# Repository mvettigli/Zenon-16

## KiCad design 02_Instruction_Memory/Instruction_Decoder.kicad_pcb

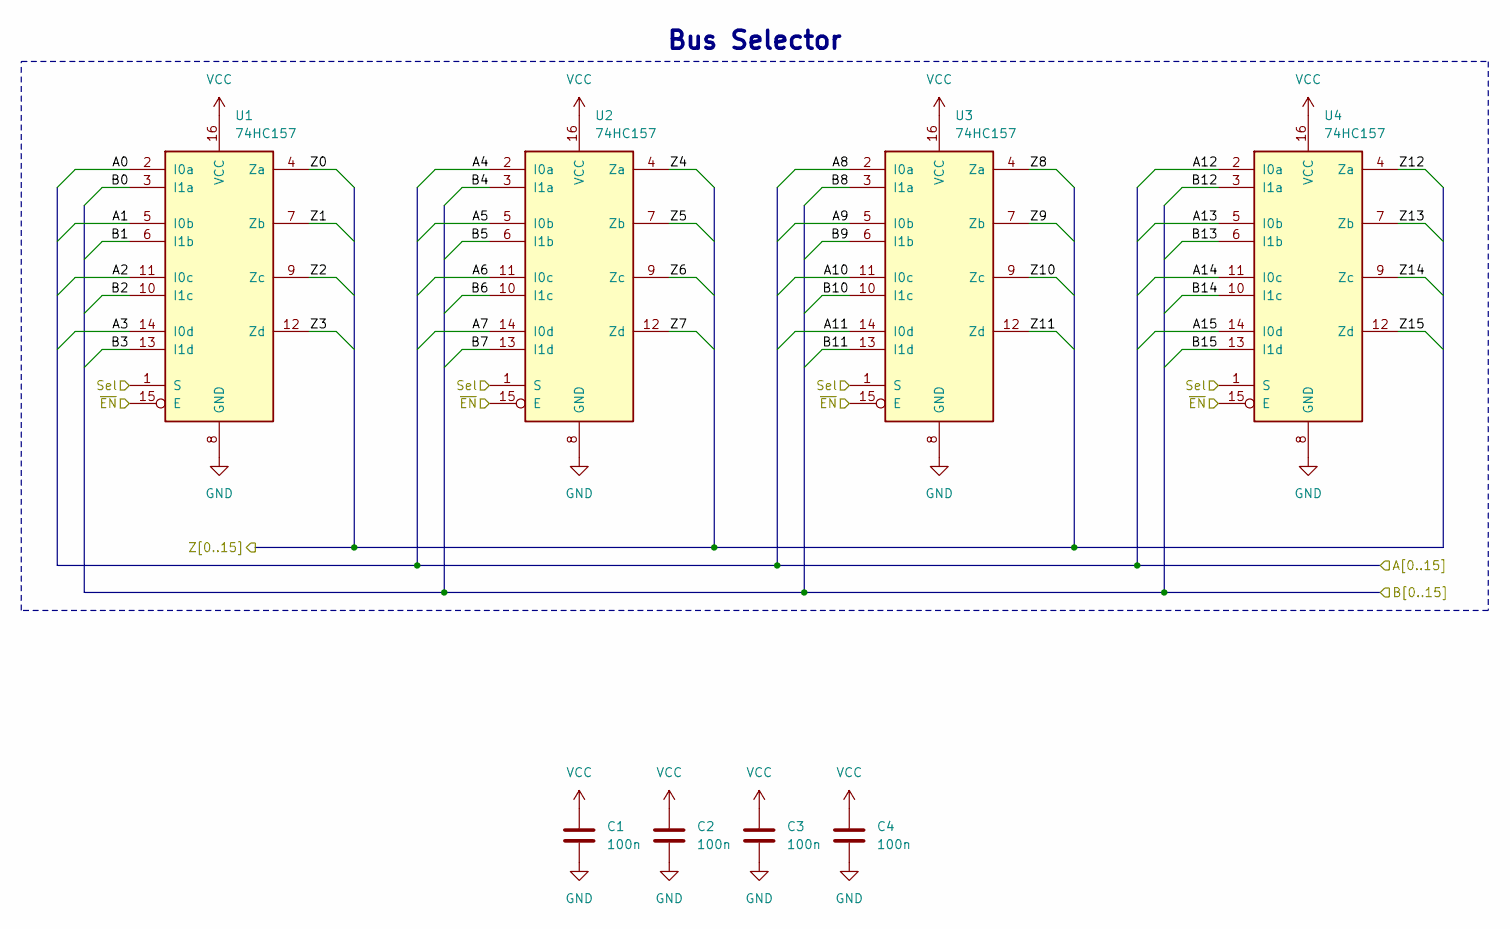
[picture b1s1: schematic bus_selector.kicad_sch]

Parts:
C1, C2, C3, C4: 100n; C_0603_1608Metric
U1, U2, U3, U4: 74HC157; TSSOP-16_4.4x5mm_P0.65mm

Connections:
/A0: U1.4 (Za); also elsewhere on the board
/A1: U1.7 (Zb); also elsewhere on the board
/A2: U1.9 (Zc); also elsewhere on the board
/A3: U1.12 (Zd); also elsewhere on the board
/A4: U2.4 (Za); also elsewhere on the board
/A5: U2.7 (Zb); also elsewhere on the board
/A6: U2.9 (Zc); also elsewhere on the board
/A7: U2.12 (Zd); also elsewhere on the board
/A8: U3.4 (Za); also elsewhere on the board
/A9: U3.7 (Zb); also elsewhere on the board
/A10: U3.9 (Zc); also elsewhere on the board
/A11: U3.12 (Zd); also elsewhere on the board
/A12: U4.4 (Za); also elsewhere on the board
/A13: U4.7 (Zb); also elsewhere on the board
/A14: U4.9 (Zc); also elsewhere on the board
/A15: U4.12 (Zd); also elsewhere on the board
/Address selector/A0: U1.2 (I0a); also elsewhere on the board
/Address selector/A1: U1.5 (I0b); also elsewhere on the board
/Address selector/A2: U1.11 (I0c); also elsewhere on the board
/Address selector/A3: U1.14 (I0d); also elsewhere on the board
/Address selector/A4: U2.2 (I0a); also elsewhere on the board
/Address selector/A5: U2.5 (I0b); also elsewhere on the board
/Address selector/A6: U2.11 (I0c); also elsewhere on the board
/Address selector/A7: U2.14 (I0d); also elsewhere on the board
/Address selector/A8: U3.2 (I0a); also elsewhere on the board
/Address selector/A9: U3.5 (I0b); also elsewhere on the board
/Address selector/A10: U3.11 (I0c); also elsewhere on the board
/Address selector/A11: U3.14 (I0d); also elsewhere on the board
/Address selector/A12: U4.2 (I0a); also elsewhere on the board
/Address selector/A13: U4.5 (I0b); also elsewhere on the board
/Address selector/A14: U4.11 (I0c); also elsewhere on the board
/Address selector/A15: U4.14 (I0d); also elsewhere on the board
/MR0: U1.3 (I1a)
/MR1: U1.6 (I1b)
/MR2: U1.10 (I1c)
/MR3: U1.13 (I1d)
/MR4: U2.3 (I1a)
/MR5: U2.6 (I1b)
/MR6: U2.10 (I1c)
/MR7: U2.13 (I1d)
/MR8: U3.3 (I1a)
/MR9: U3.6 (I1b)
/MR10: U3.10 (I1c)
/MR11: U3.13 (I1d)
/MR12: U4.3 (I1a)
/MR13: U4.6 (I1b)
/MR14: U4.10 (I1c)
/MR15: U4.13 (I1d)
~PC/MR: U1.1 (S), U2.1 (S), U3.1 (S), U4.1 (S)

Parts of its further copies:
C16, C17, C18, C19, C26, C27, C28, C29: 100n; C_0603_1608Metric
U15, U16, U17, U18, U25, U26, U27, U28: 74HC157; TSSOP-16_4.4x5mm_P0.65mm

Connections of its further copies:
/ImR0: U25.2 (I0a); also elsewhere on the board
/ImR1: U25.5 (I0b); also elsewhere on the board
/ImR2: U25.11 (I0c); also elsewhere on the board
/ImR3: U25.14 (I0d); also elsewhere on the board
/ImR4: U26.2 (I0a); also elsewhere on the board
/ImR5: U26.5 (I0b); also elsewhere on the board
/ImR6: U26.11 (I0c); also elsewhere on the board
/ImR7: U26.14 (I0d); also elsewhere on the board
/ImR8: U27.2 (I0a); also elsewhere on the board
/ImR9: U27.5 (I0b); also elsewhere on the board
/ImR10: U27.11 (I0c); also elsewhere on the board
/ImR11: U27.14 (I0d); also elsewhere on the board
/ImR12: U28.2 (I0a); also elsewhere on the board
/ImR13: U28.5 (I0b); also elsewhere on the board
/ImR14: U28.11 (I0c); also elsewhere on the board
/ImR15: U28.14 (I0d); also elsewhere on the board
/InR0: U15.3 (I1a); also elsewhere on the board
/InR1: U15.6 (I1b); also elsewhere on the board
/InR2: U15.10 (I1c); also elsewhere on the board
/InR3: U15.13 (I1d); also elsewhere on the board
/InR4: U16.3 (I1a); also elsewhere on the board
/InR5: U16.6 (I1b); also elsewhere on the board
/InR6: U16.10 (I1c); also elsewhere on the board
/InR7: U16.13 (I1d); also elsewhere on the board
/InR8: U17.3 (I1a); also elsewhere on the board
/InR9: U17.6 (I1b); also elsewhere on the board
/InR10: U17.10 (I1c); also elsewhere on the board
/InR11: U17.13 (I1d); also elsewhere on the board
/InR12: U18.3 (I1a); also elsewhere on the board
/InR13: U18.6 (I1b); also elsewhere on the board
/InR14: U18.10 (I1c); also elsewhere on the board
/InR15: U18.13 (I1d); also elsewhere on the board
/Program counter/1R0: U15.2 (I0a)
/Program counter/1R1: U15.5 (I0b)
/Program counter/1R2: U15.11 (I0c)
/Program counter/1R3: U15.14 (I0d)
/Program counter/1R4: U16.2 (I0a)
/Program counter/1R5: U16.5 (I0b)
/Program counter/1R6: U16.11 (I0c)
/Program counter/1R7: U16.14 (I0d)
/Program counter/1R8: U17.2 (I0a)
/Program counter/1R9: U17.5 (I0b)
/Program counter/1R10: U17.11 (I0c)
/Program counter/1R11: U17.14 (I0d)
/Program counter/1R12: U18.2 (I0a)
/Program counter/1R13: U18.5 (I0b)
/Program counter/1R14: U18.11 (I0c)
/Program counter/1R15: U18.14 (I0d)
/Program counter/B0: U15.4 (Za); also elsewhere on the board
/Program counter/B1: U15.7 (Zb); also elsewhere on the board
/Program counter/B2: U15.9 (Zc); also elsewhere on the board
/Program counter/B3: U15.12 (Zd); also elsewhere on the board
/Program counter/B4: U16.4 (Za); also elsewhere on the board
/Program counter/B5: U16.7 (Zb); also elsewhere on the board
/Program counter/B6: U16.9 (Zc); also elsewhere on the board
/Program counter/B7: U16.12 (Zd); also elsewhere on the board
/Program counter/B8: U17.4 (Za); also elsewhere on the board
/Program counter/B9: U17.7 (Zb); also elsewhere on the board
/Program counter/B10: U17.9 (Zc); also elsewhere on the board
/Program counter/B11: U17.12 (Zd); also elsewhere on the board
/Program counter/B12: U18.4 (Za); also elsewhere on the board
/Program counter/B13: U18.7 (Zb); also elsewhere on the board
/Program counter/B14: U18.9 (Zc); also elsewhere on the board
/Program counter/B15: U18.12 (Zd); also elsewhere on the board
/Program counter/D0: U25.4 (Za); also elsewhere on the board
/Program counter/D1: U25.7 (Zb); also elsewhere on the board
/Program counter/D2: U25.9 (Zc); also elsewhere on the board
/Program counter/D3: U25.12 (Zd); also elsewhere on the board
/Program counter/D4: U26.4 (Za); also elsewhere on the board
/Program counter/D5: U26.7 (Zb); also elsewhere on the board
/Program counter/D6: U26.9 (Zc); also elsewhere on the board
/Program counter/D7: U26.12 (Zd); also elsewhere on the board
/Program counter/D8: U27.4 (Za); also elsewhere on the board
/Program counter/D9: U27.7 (Zb); also elsewhere on the board
/Program counter/D10: U27.9 (Zc); also elsewhere on the board
/Program counter/D11: U27.12 (Zd); also elsewhere on the board
/Program counter/D12: U28.4 (Za); also elsewhere on the board
/Program counter/D13: U28.7 (Zb); also elsewhere on the board
/Program counter/D14: U28.9 (Zc); also elsewhere on the board
/Program counter/D15: U28.12 (Zd); also elsewhere on the board
/Program counter/RST: U25.15 (E), U26.15 (E), U27.15 (E), U28.15 (E)
/Program counter/S0: U25.3 (I1a); also elsewhere on the board
/Program counter/S1: U25.6 (I1b); also elsewhere on the board
/Program counter/S2: U25.10 (I1c); also elsewhere on the board
/Program counter/S3: U25.13 (I1d); also elsewhere on the board
/Program counter/S4: U26.3 (I1a); also elsewhere on the board
/Program counter/S5: U26.6 (I1b); also elsewhere on the board
/Program counter/S6: U26.10 (I1c); also elsewhere on the board
/Program counter/S7: U26.13 (I1d); also elsewhere on the board
/Program counter/S8: U27.3 (I1a); also elsewhere on the board
/Program counter/S9: U27.6 (I1b); also elsewhere on the board
/Program counter/S10: U27.10 (I1c); also elsewhere on the board
/Program counter/S11: U27.13 (I1d); also elsewhere on the board
/Program counter/S12: U28.3 (I1a); also elsewhere on the board
/Program counter/S13: U28.6 (I1b); also elsewhere on the board
/Program counter/S14: U28.10 (I1c); also elsewhere on the board
/Program counter/S15: U28.13 (I1d); also elsewhere on the board
/Program counter/~Abs: U25.1 (S), U26.1 (S), U27.1 (S), U28.1 (S)
/Program counter/~CE: U15.1 (S), U16.1 (S), U17.1 (S), U18.1 (S)

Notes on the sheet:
Bus Selector

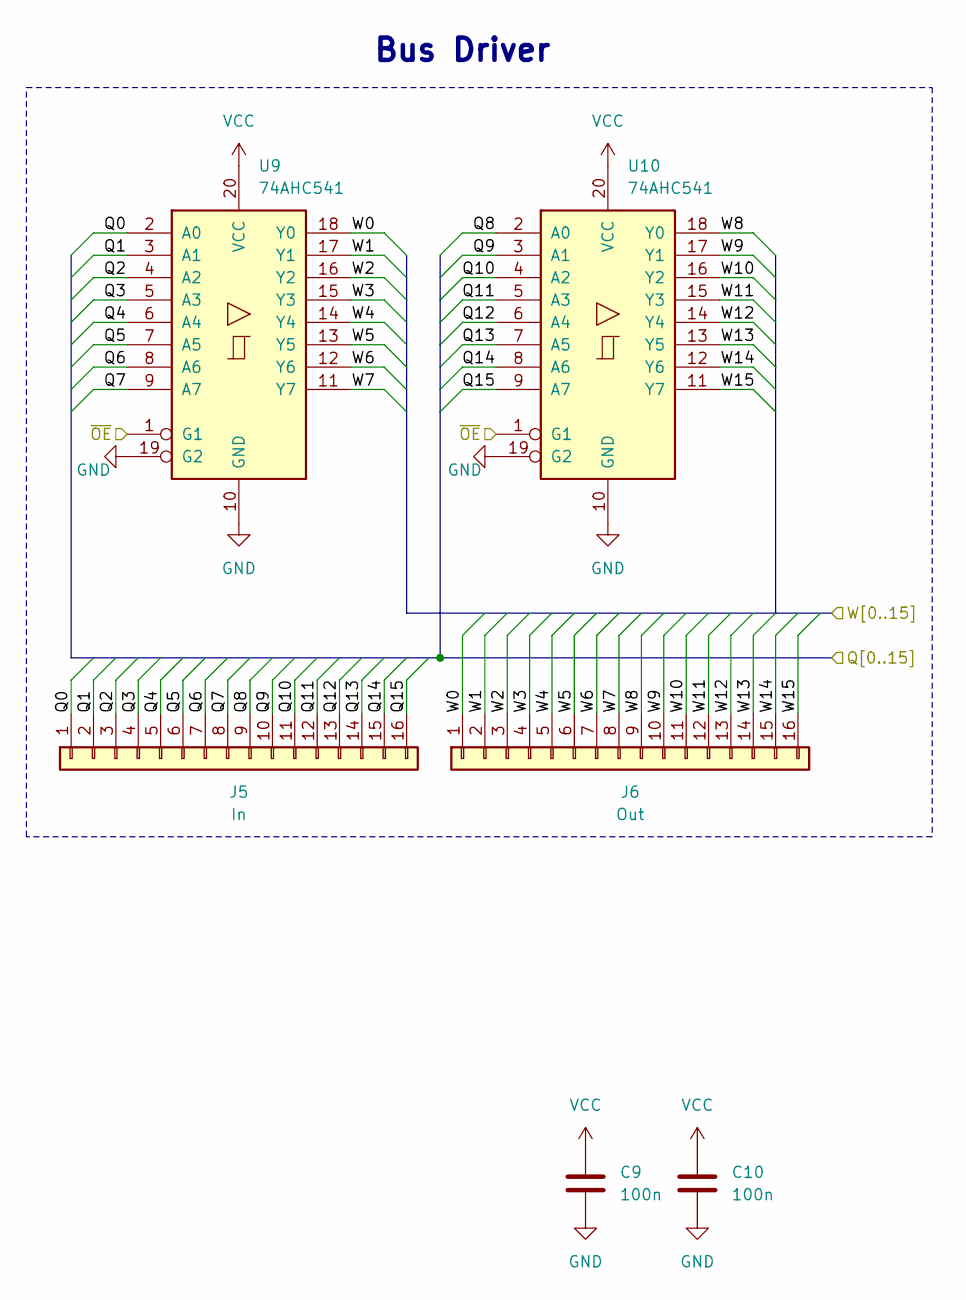
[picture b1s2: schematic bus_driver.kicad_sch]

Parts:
C9, C10: 100n; C_0603_1608Metric
J5: In; Conn_01x16_p=0.6um
J6: Out; Conn_01x16_p=0.6um
U9, U10: 74AHC541; TSSOP-20_4.4x6.5mm_P0.65mm

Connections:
/Flash Y-Bus/W0: J6.1, U9.18 (Y0)
/Flash Y-Bus/W1: J6.2, U9.17 (Y1)
/Flash Y-Bus/W2: J6.3, U9.16 (Y2)
/Flash Y-Bus/W3: J6.4, U9.15 (Y3)
/Flash Y-Bus/W4: J6.5, U9.14 (Y4)
/Flash Y-Bus/W5: J6.6, U9.13 (Y5)
/Flash Y-Bus/W6: J6.7, U9.12 (Y6)
/Flash Y-Bus/W7: J6.8, U9.11 (Y7)
/Flash Y-Bus/W8: J6.9, U10.18 (Y0)
/Flash Y-Bus/W9: J6.10, U10.17 (Y1)
/Flash Y-Bus/W10: J6.11, U10.16 (Y2)
/Flash Y-Bus/W11: J6.12, U10.15 (Y3)
/Flash Y-Bus/W12: J6.13, U10.14 (Y4)
/Flash Y-Bus/W13: J6.14, U10.13 (Y5)
/Flash Y-Bus/W14: J6.15, U10.12 (Y6)
/Flash Y-Bus/W15: J6.16, U10.11 (Y7)
/Flash Y-Bus/~OE: U9.1 (G1), U10.1 (G1)
/WBus6: J5.7, U9.8 (A6); also elsewhere on the board
/WBus7: J5.8, U9.9 (A7); also elsewhere on the board
/WBus8: J5.9, U10.2 (A0); also elsewhere on the board
/WBus9: J5.10, U10.3 (A1); also elsewhere on the board
/WBus10: J5.11, U10.4 (A2); also elsewhere on the board
/WBus11: J5.12, U10.5 (A3); also elsewhere on the board
/WBus12: J5.13, U10.6 (A4); also elsewhere on the board
/WBus13: J5.14, U10.7 (A5); also elsewhere on the board
/WBus14: J5.15, U10.8 (A6); also elsewhere on the board
/WBus15: J5.16, U10.9 (A7); also elsewhere on the board

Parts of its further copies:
C11, C12, C13, C14: 100n; C_0603_1608Metric
J7, J9: In; Conn_01x16_p=0.6um
J8, J10: Out; Conn_01x16_p=0.6um
U11, U12, U13, U14: 74AHC541; TSSOP-20_4.4x6.5mm_P0.65mm

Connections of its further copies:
/ImR0: J7.1, U11.2 (A0); also elsewhere on the board
/ImR1: J7.2, U11.3 (A1); also elsewhere on the board
/ImR2: J7.3, U11.4 (A2); also elsewhere on the board
/ImR3: J7.4, U11.5 (A3); also elsewhere on the board
/ImR4: J7.5, U11.6 (A4); also elsewhere on the board
/ImR5: J7.6, U11.7 (A5); also elsewhere on the board
/ImR6: J7.7, U11.8 (A6); also elsewhere on the board
/ImR7: J7.8, U11.9 (A7); also elsewhere on the board
/ImR8: J7.9, U12.2 (A0); also elsewhere on the board
/ImR9: J7.10, U12.3 (A1); also elsewhere on the board
/ImR10: J7.11, U12.4 (A2); also elsewhere on the board
/ImR11: J7.12, U12.5 (A3); also elsewhere on the board
/ImR12: J7.13, U12.6 (A4); also elsewhere on the board
/ImR13: J7.14, U12.7 (A5); also elsewhere on the board
/ImR14: J7.15, U12.8 (A6); also elsewhere on the board
/ImR15: J7.16, U12.9 (A7); also elsewhere on the board
/Immediate Y-bus/~OE: U11.1 (G1), U12.1 (G1)
/InR0: J9.1, U13.2 (A0); also elsewhere on the board
/InR1: J9.2, U13.3 (A1); also elsewhere on the board
/InR2: J9.3, U13.4 (A2); also elsewhere on the board
/InR3: J9.4, U13.5 (A3); also elsewhere on the board
/InR4: J9.5, U13.6 (A4); also elsewhere on the board
/InR5: J9.6, U13.7 (A5); also elsewhere on the board
/InR6: J9.7, U13.8 (A6); also elsewhere on the board
/InR7: J9.8, U13.9 (A7); also elsewhere on the board
/InR8: J9.9, U14.2 (A0); also elsewhere on the board
/InR9: J9.10, U14.3 (A1); also elsewhere on the board
/InR10: J9.11, U14.4 (A2); also elsewhere on the board
/InR11: J9.12, U14.5 (A3); also elsewhere on the board
/InR12: J9.13, U14.6 (A4); also elsewhere on the board
/InR13: J9.14, U14.7 (A5); also elsewhere on the board
/InR14: J9.15, U14.8 (A6); also elsewhere on the board
/InR15: J9.16, U14.9 (A7); also elsewhere on the board
/Instruction Y-Bus/~OE: U13.1 (G1), U14.1 (G1)
/YBus0: J8.1, J10.1, U11.18 (Y0), U13.18 (Y0)
/YBus1: J8.2, J10.2, U11.17 (Y1), U13.17 (Y1)
/YBus2: J8.3, J10.3, U11.16 (Y2), U13.16 (Y2)
/YBus3: J8.4, J10.4, U11.15 (Y3), U13.15 (Y3)
/YBus4: J8.5, J10.5, U11.14 (Y4), U13.14 (Y4)
/YBus5: J8.6, J10.6, U11.13 (Y5), U13.13 (Y5)
/YBus6: J8.7, J10.7, U11.12 (Y6), U13.12 (Y6)
/YBus7: J8.8, J10.8, U11.11 (Y7), U13.11 (Y7)
/YBus8: J8.9, J10.9, U12.18 (Y0), U14.18 (Y0)
/YBus9: J8.10, J10.10, U12.17 (Y1), U14.17 (Y1)
/YBus10: J8.11, J10.11, U12.16 (Y2), U14.16 (Y2)
/YBus11: J8.12, J10.12, U12.15 (Y3), U14.15 (Y3)
/YBus12: J8.13, J10.13, U12.14 (Y4), U14.14 (Y4)
/YBus13: J8.14, J10.14, U12.13 (Y5), U14.13 (Y5)
/YBus14: J8.15, J10.15, U12.12 (Y6), U14.12 (Y6)
/YBus15: J8.16, J10.16, U12.11 (Y7), U14.11 (Y7)

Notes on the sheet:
Bus Driver

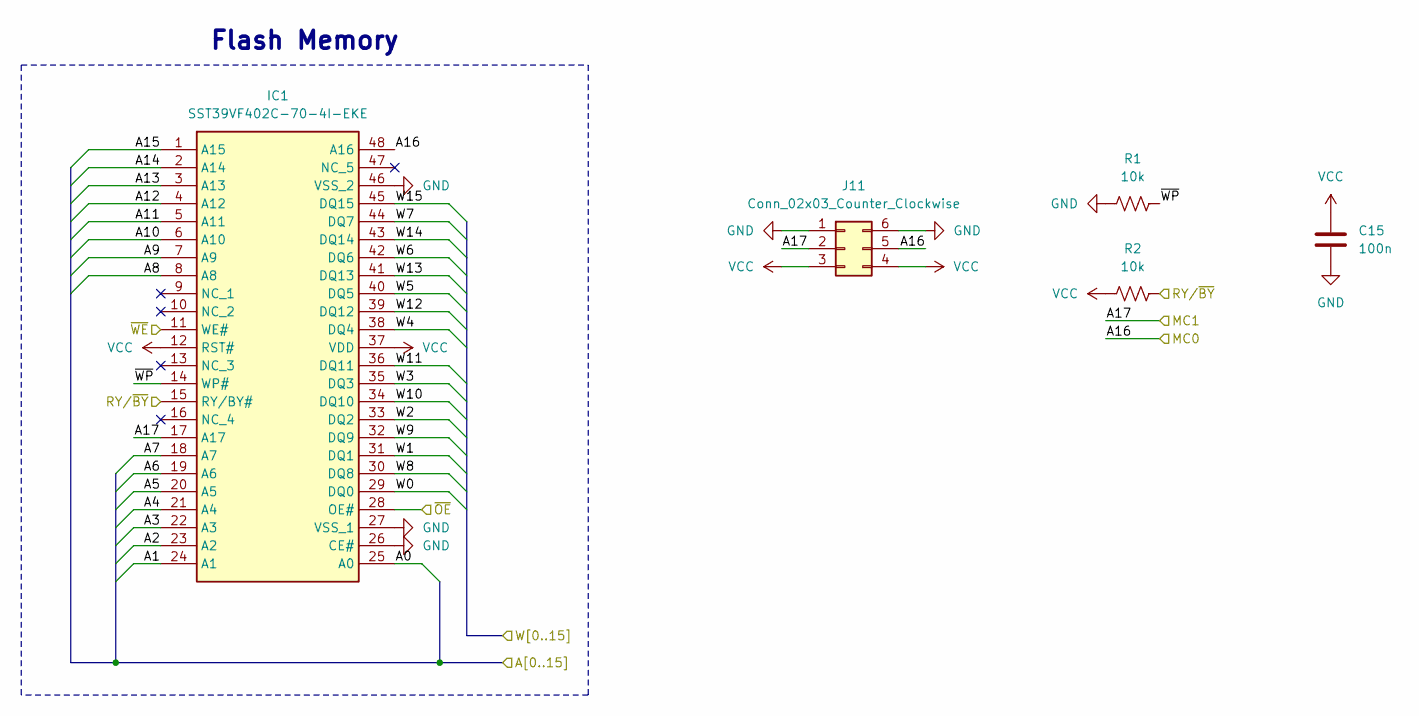
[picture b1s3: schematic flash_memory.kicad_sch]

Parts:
C15: 100n; C_0603_1608Metric
IC1: SST39VF402C-70-4I-EKE; SOP50P2000X120-48N; Mouser Part Number 579-S39VF402C704IEKE
J11: Conn_02x03_Counter_Clockwise
R1, R2: 10k

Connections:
/A0: IC1.25 (A0); also elsewhere on the board
/A1: IC1.24 (A1); also elsewhere on the board
/A2: IC1.23 (A2); also elsewhere on the board
/A3: IC1.22 (A3); also elsewhere on the board
/A4: IC1.21 (A4); also elsewhere on the board
/A5: IC1.20 (A5); also elsewhere on the board
/A6: IC1.19 (A6); also elsewhere on the board
/A7: IC1.18 (A7); also elsewhere on the board
/A8: IC1.8 (A8); also elsewhere on the board
/A9: IC1.7 (A9); also elsewhere on the board
/A10: IC1.6 (A10); also elsewhere on the board
/A11: IC1.5 (A11); also elsewhere on the board
/A12: IC1.4 (A12); also elsewhere on the board
/A13: IC1.3 (A13); also elsewhere on the board
/A14: IC1.2 (A14); also elsewhere on the board
/A15: IC1.1 (A15); also elsewhere on the board
/Flash memory/RY/~BY: IC1.15 (RY/BY#), R2.2
/Flash memory/~WP: IC1.14 (WP#), R1.2
/WBus6: IC1.42 (DQ6); also elsewhere on the board
/WBus7: IC1.44 (DQ7); also elsewhere on the board
/WBus8: IC1.30 (DQ8); also elsewhere on the board
/WBus9: IC1.32 (DQ9); also elsewhere on the board
/WBus10: IC1.34 (DQ10); also elsewhere on the board
/WBus11: IC1.36 (DQ11); also elsewhere on the board
/WBus12: IC1.39 (DQ12); also elsewhere on the board
/WBus13: IC1.41 (DQ13); also elsewhere on the board
/WBus14: IC1.43 (DQ14); also elsewhere on the board
/WBus15: IC1.45 (DQ15); also elsewhere on the board
~FlMO: IC1.28 (OE#)
~FlMW: IC1.11 (WE#)

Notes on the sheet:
Flash Memory

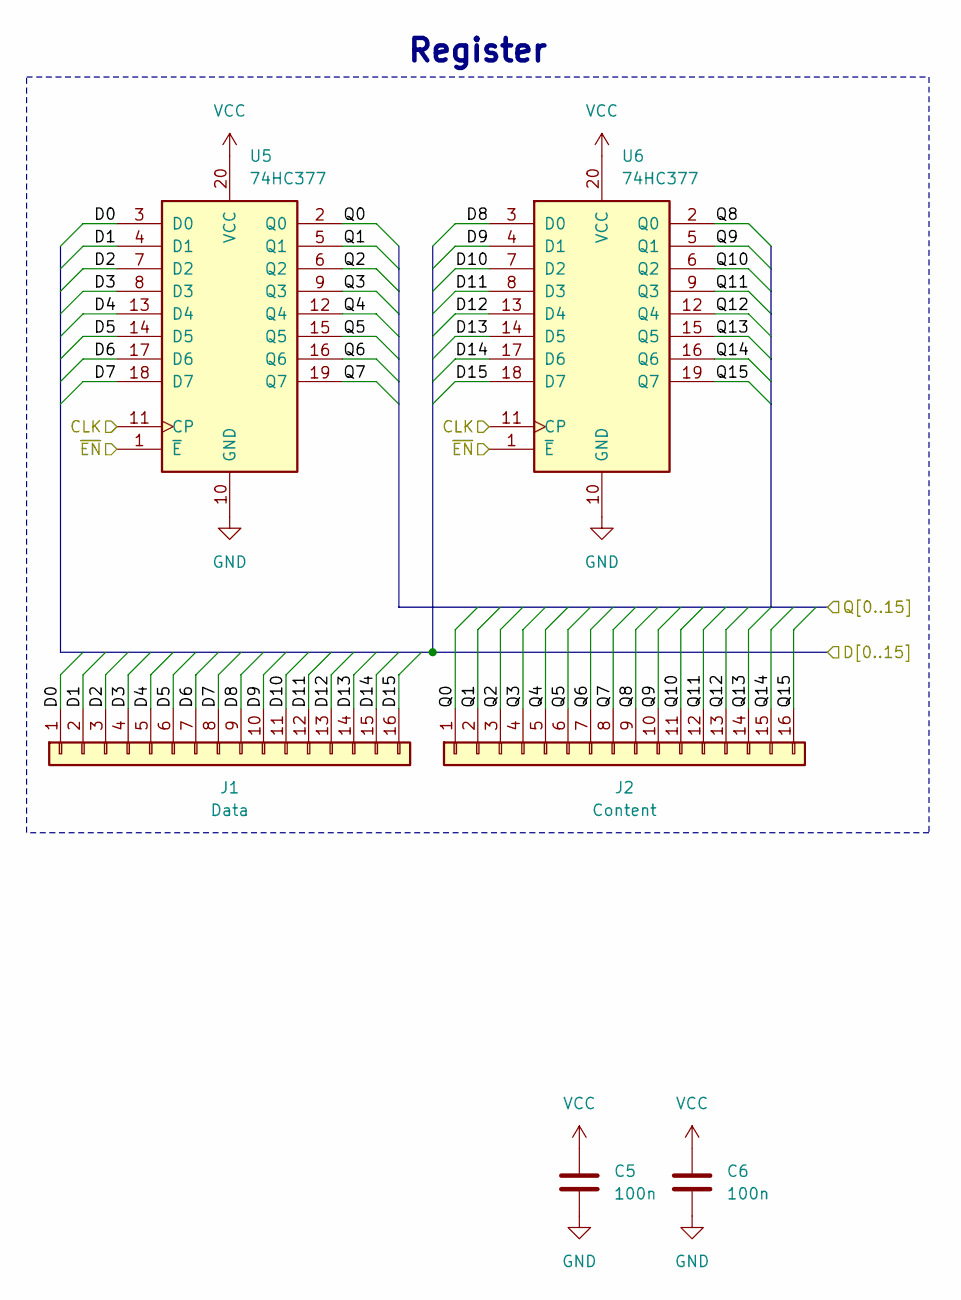
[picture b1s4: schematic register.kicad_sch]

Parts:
C5, C6: 100n; C_0603_1608Metric
J1: Data; Conn_01x16_p=0.6um
J2: Content; Conn_01x16_p=0.6um
U5, U6: 74HC377; TSSOP-20_4.4x6.5mm_P0.65mm

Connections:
/InR0: J2.1, U5.2 (Q0); also elsewhere on the board
/InR1: J2.2, U5.5 (Q1); also elsewhere on the board
/InR2: J2.3, U5.6 (Q2); also elsewhere on the board
/InR3: J2.4, U5.9 (Q3); also elsewhere on the board
/InR4: J2.5, U5.12 (Q4); also elsewhere on the board
/InR5: J2.6, U5.15 (Q5); also elsewhere on the board
/InR6: J2.7, U5.16 (Q6); also elsewhere on the board
/InR7: J2.8, U5.19 (Q7); also elsewhere on the board
/InR8: J2.9, U6.2 (Q0); also elsewhere on the board
/InR9: J2.10, U6.5 (Q1); also elsewhere on the board
/InR10: J2.11, U6.6 (Q2); also elsewhere on the board
/InR11: J2.12, U6.9 (Q3); also elsewhere on the board
/InR12: J2.13, U6.12 (Q4); also elsewhere on the board
/InR13: J2.14, U6.15 (Q5); also elsewhere on the board
/InR14: J2.15, U6.16 (Q6); also elsewhere on the board
/InR15: J2.16, U6.19 (Q7); also elsewhere on the board
/WBus6: J1.7, U5.17 (D6); also elsewhere on the board
/WBus7: J1.8, U5.18 (D7); also elsewhere on the board
/WBus8: J1.9, U6.3 (D0); also elsewhere on the board
/WBus9: J1.10, U6.4 (D1); also elsewhere on the board
/WBus10: J1.11, U6.7 (D2); also elsewhere on the board
/WBus11: J1.12, U6.8 (D3); also elsewhere on the board
/WBus12: J1.13, U6.13 (D4); also elsewhere on the board
/WBus13: J1.14, U6.14 (D5); also elsewhere on the board
/WBus14: J1.15, U6.17 (D6); also elsewhere on the board
/WBus15: J1.16, U6.18 (D7); also elsewhere on the board
CLK: U5.11 (CP), U6.11 (CP); also elsewhere on the board
~InRW: U5.1 (~E), U6.1 (~E)

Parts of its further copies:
C7, C8, C16, C24, C25: 100n; C_0603_1608Metric
J3, J14: Data; Conn_01x16_p=0.6um
J4, J15: Content; Conn_01x16_p=0.6um
U7, U8, U23, U24: 74HC377; TSSOP-20_4.4x6.5mm_P0.65mm

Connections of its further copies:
/Address selector/A0: J15.1, U23.2 (Q0); also elsewhere on the board
/Address selector/A1: J15.2, U23.5 (Q1); also elsewhere on the board
/Address selector/A2: J15.3, U23.6 (Q2); also elsewhere on the board
/Address selector/A3: J15.4, U23.9 (Q3); also elsewhere on the board
/Address selector/A4: J15.5, U23.12 (Q4); also elsewhere on the board
/Address selector/A5: J15.6, U23.15 (Q5); also elsewhere on the board
/Address selector/A6: J15.7, U23.16 (Q6); also elsewhere on the board
/Address selector/A7: J15.8, U23.19 (Q7); also elsewhere on the board
/Address selector/A8: J15.9, U24.2 (Q0); also elsewhere on the board
/Address selector/A9: J15.10, U24.5 (Q1); also elsewhere on the board
/Address selector/A10: J15.11, U24.6 (Q2); also elsewhere on the board
/Address selector/A11: J15.12, U24.9 (Q3); also elsewhere on the board
/Address selector/A12: J15.13, U24.12 (Q4); also elsewhere on the board
/Address selector/A13: J15.14, U24.15 (Q5); also elsewhere on the board
/Address selector/A14: J15.15, U24.16 (Q6); also elsewhere on the board
/Address selector/A15: J15.16, U24.19 (Q7); also elsewhere on the board
/ImR0: J4.1, U7.2 (Q0); also elsewhere on the board
/ImR1: J4.2, U7.5 (Q1); also elsewhere on the board
/ImR2: J4.3, U7.6 (Q2); also elsewhere on the board
/ImR3: J4.4, U7.9 (Q3); also elsewhere on the board
/ImR4: J4.5, U7.12 (Q4); also elsewhere on the board
/ImR5: J4.6, U7.15 (Q5); also elsewhere on the board
/ImR6: J4.7, U7.16 (Q6); also elsewhere on the board
/ImR7: J4.8, U7.19 (Q7); also elsewhere on the board
/ImR8: J4.9, U8.2 (Q0); also elsewhere on the board
/ImR9: J4.10, U8.5 (Q1); also elsewhere on the board
/ImR10: J4.11, U8.6 (Q2); also elsewhere on the board
/ImR11: J4.12, U8.9 (Q3); also elsewhere on the board
/ImR12: J4.13, U8.12 (Q4); also elsewhere on the board
/ImR13: J4.14, U8.15 (Q5); also elsewhere on the board
/ImR14: J4.15, U8.16 (Q6); also elsewhere on the board
/ImR15: J4.16, U8.19 (Q7); also elsewhere on the board
/Program counter/CLK: U23.11 (CP), U24.11 (CP)
/Program counter/D0: J14.1, U23.3 (D0); also elsewhere on the board
/Program counter/D1: J14.2, U23.4 (D1); also elsewhere on the board
/Program counter/D2: J14.3, U23.7 (D2); also elsewhere on the board
/Program counter/D3: J14.4, U23.8 (D3); also elsewhere on the board
/Program counter/D4: J14.5, U23.13 (D4); also elsewhere on the board
/Program counter/D5: J14.6, U23.14 (D5); also elsewhere on the board
/Program counter/D6: J14.7, U23.17 (D6); also elsewhere on the board
/Program counter/D7: J14.8, U23.18 (D7); also elsewhere on the board
/Program counter/D8: J14.9, U24.3 (D0); also elsewhere on the board
/Program counter/D9: J14.10, U24.4 (D1); also elsewhere on the board
/Program counter/D10: J14.11, U24.7 (D2); also elsewhere on the board
/Program counter/D11: J14.12, U24.8 (D3); also elsewhere on the board
/Program counter/D12: J14.13, U24.13 (D4); also elsewhere on the board
/Program counter/D13: J14.14, U24.14 (D5); also elsewhere on the board
/Program counter/D14: J14.15, U24.17 (D6); also elsewhere on the board
/Program counter/D15: J14.16, U24.18 (D7); also elsewhere on the board
/Program counter/~EN: U23.1 (~E), U24.1 (~E)
/WBus6: J3.7, U7.17 (D6); also elsewhere on the board
/WBus7: J3.8, U7.18 (D7); also elsewhere on the board
/WBus8: J3.9, U8.3 (D0); also elsewhere on the board
/WBus9: J3.10, U8.4 (D1); also elsewhere on the board
/WBus10: J3.11, U8.7 (D2); also elsewhere on the board
/WBus11: J3.12, U8.8 (D3); also elsewhere on the board
/WBus12: J3.13, U8.13 (D4); also elsewhere on the board
/WBus13: J3.14, U8.14 (D5); also elsewhere on the board
/WBus14: J3.15, U8.17 (D6); also elsewhere on the board
/WBus15: J3.16, U8.18 (D7); also elsewhere on the board
CLK: U7.11 (CP), U8.11 (CP); also elsewhere on the board
~ImRW: U7.1 (~E), U8.1 (~E)

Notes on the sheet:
Register

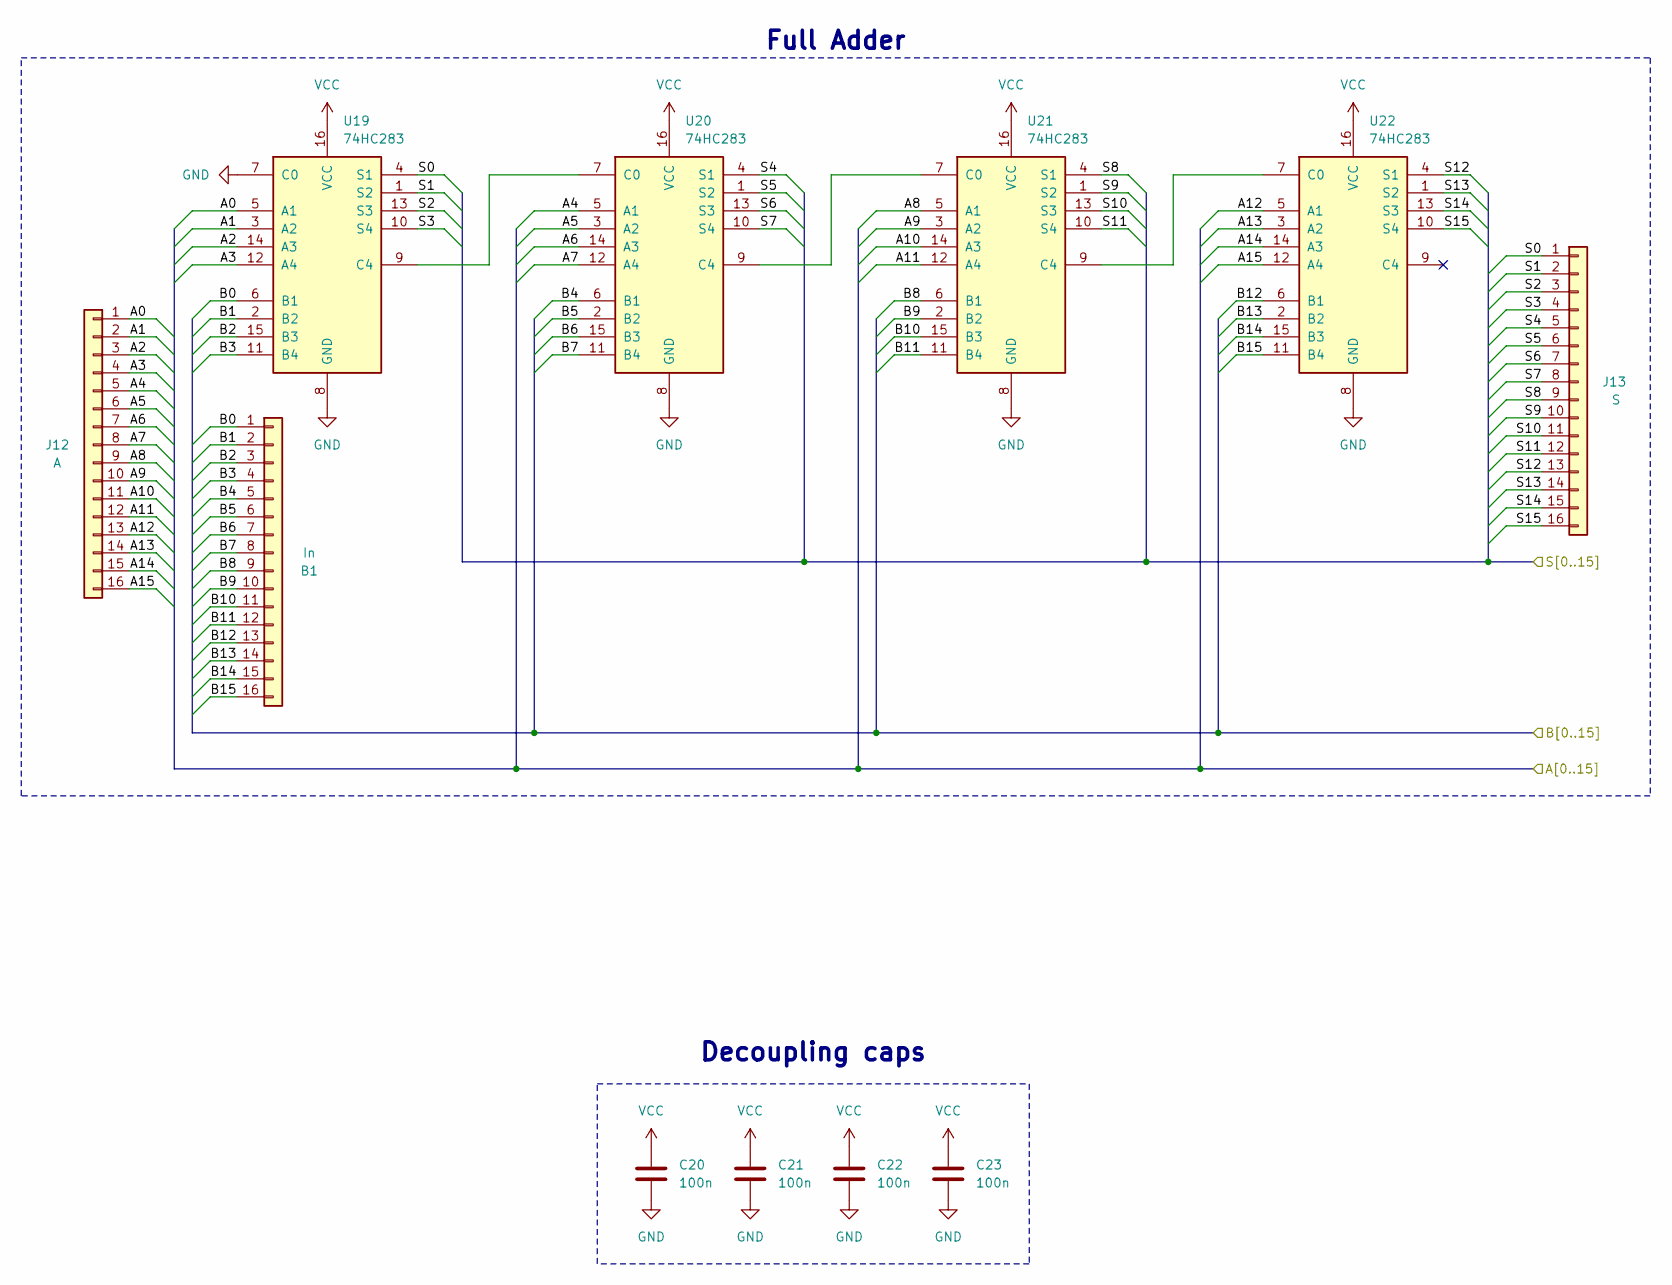
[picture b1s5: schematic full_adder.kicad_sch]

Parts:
B1: In; Conn_01x16_p=0.6um
C20, C21, C22, C23: 100n; C_0603_1608Metric
J12: A; Conn_01x16_p=0.6um
J13: S; Conn_01x16_p=0.6um
U19, U20, U21, U22: 74HC283; SOIC-16_3.9x9.9mm_P1.27mm

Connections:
/Address selector/A0: J12.1, U19.5 (A1); also elsewhere on the board
/Address selector/A1: J12.2, U19.3 (A2); also elsewhere on the board
/Address selector/A2: J12.3, U19.14 (A3); also elsewhere on the board
/Address selector/A3: J12.4, U19.12 (A4); also elsewhere on the board
/Address selector/A4: J12.5, U20.5 (A1); also elsewhere on the board
/Address selector/A5: J12.6, U20.3 (A2); also elsewhere on the board
/Address selector/A6: J12.7, U20.14 (A3); also elsewhere on the board
/Address selector/A7: J12.8, U20.12 (A4); also elsewhere on the board
/Address selector/A8: J12.9, U21.5 (A1); also elsewhere on the board
/Address selector/A9: J12.10, U21.3 (A2); also elsewhere on the board
/Address selector/A10: J12.11, U21.14 (A3); also elsewhere on the board
/Address selector/A11: J12.12, U21.12 (A4); also elsewhere on the board
/Address selector/A12: J12.13, U22.5 (A1); also elsewhere on the board
/Address selector/A13: J12.14, U22.3 (A2); also elsewhere on the board
/Address selector/A14: J12.15, U22.14 (A3); also elsewhere on the board
/Address selector/A15: J12.16, U22.12 (A4); also elsewhere on the board
/Program counter/B0: B1.1, U19.6 (B1); also elsewhere on the board
/Program counter/B1: B1.2, U19.2 (B2); also elsewhere on the board
/Program counter/B2: B1.3, U19.15 (B3); also elsewhere on the board
/Program counter/B3: B1.4, U19.11 (B4); also elsewhere on the board
/Program counter/B4: B1.5, U20.6 (B1); also elsewhere on the board
/Program counter/B5: B1.6, U20.2 (B2); also elsewhere on the board
/Program counter/B6: B1.7, U20.15 (B3); also elsewhere on the board
/Program counter/B7: B1.8, U20.11 (B4); also elsewhere on the board
/Program counter/B8: B1.9, U21.6 (B1); also elsewhere on the board
/Program counter/B9: B1.10, U21.2 (B2); also elsewhere on the board
/Program counter/B10: B1.11, U21.15 (B3); also elsewhere on the board
/Program counter/B11: B1.12, U21.11 (B4); also elsewhere on the board
/Program counter/B12: B1.13, U22.6 (B1); also elsewhere on the board
/Program counter/B13: B1.14, U22.2 (B2); also elsewhere on the board
/Program counter/B14: B1.15, U22.15 (B3); also elsewhere on the board
/Program counter/B15: B1.16, U22.11 (B4); also elsewhere on the board
/Program counter/S0: J13.1, U19.4 (S1); also elsewhere on the board
/Program counter/S1: J13.2, U19.1 (S2); also elsewhere on the board
/Program counter/S2: J13.3, U19.13 (S3); also elsewhere on the board
/Program counter/S3: J13.4, U19.10 (S4); also elsewhere on the board
/Program counter/S4: J13.5, U20.4 (S1); also elsewhere on the board
/Program counter/S5: J13.6, U20.1 (S2); also elsewhere on the board
/Program counter/S6: J13.7, U20.13 (S3); also elsewhere on the board
/Program counter/S7: J13.8, U20.10 (S4); also elsewhere on the board
/Program counter/S8: J13.9, U21.4 (S1); also elsewhere on the board
/Program counter/S9: J13.10, U21.1 (S2); also elsewhere on the board
/Program counter/S10: J13.11, U21.13 (S3); also elsewhere on the board
/Program counter/S11: J13.12, U21.10 (S4); also elsewhere on the board
/Program counter/S12: J13.13, U22.4 (S1); also elsewhere on the board
/Program counter/S13: J13.14, U22.1 (S2); also elsewhere on the board
/Program counter/S14: J13.15, U22.13 (S3); also elsewhere on the board
/Program counter/S15: J13.16, U22.10 (S4); also elsewhere on the board
unnamed: U19.9 (C4), U20.7 (C0)
unnamed: U20.9 (C4), U21.7 (C0)
unnamed: U21.9 (C4), U22.7 (C0)

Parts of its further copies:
C7, C8: 100n; C_0603_1608Metric

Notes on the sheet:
Full Adder
Decoupling caps

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
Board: 4 copper layers, 73 parts (0 on the bottom side), 177 nets, no tracks yet.

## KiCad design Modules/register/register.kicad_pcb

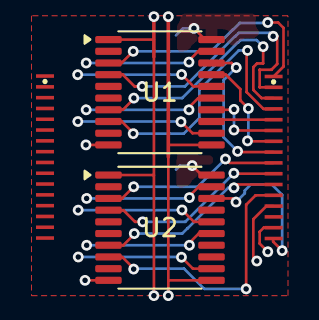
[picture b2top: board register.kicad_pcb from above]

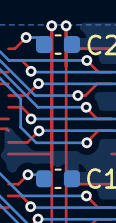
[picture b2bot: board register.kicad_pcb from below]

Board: 4 copper layers, 6 parts (2 on the bottom side), 36 nets.

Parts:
C1, C2: 100n; C_0603_1608Metric
J1: Data; Conn_01x16_p=0.6um
J2: Content; Conn_01x16_p=0.6um
U1, U2: 74HC377; TSSOP-20_4.4x6.5mm_P0.65mm

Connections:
/CLK: U1.11 (CP), U2.11 (CP)
/D0: J1.1, U1.3 (D0)
/D1: J1.2, U1.4 (D1)
/D2: J1.3, U1.7 (D2)
/D3: J1.4, U1.8 (D3)
/D4: J1.5, U1.13 (D4)
/D5: J1.6, U1.14 (D5)
/D6: J1.7, U1.17 (D6)
/D7: J1.8, U1.18 (D7)
/D8: J1.9, U2.3 (D0)
/D9: J1.10, U2.4 (D1)
/D10: J1.11, U2.7 (D2)
/D11: J1.12, U2.8 (D3)
/D12: J1.13, U2.13 (D4)
/D13: J1.14, U2.14 (D5)
/D14: J1.15, U2.17 (D6)
/D15: J1.16, U2.18 (D7)
/Q0: J2.1, U1.2 (Q0)
/Q1: J2.2, U1.5 (Q1)
/Q2: J2.3, U1.6 (Q2)
/Q3: J2.4, U1.9 (Q3)
/Q4: J2.5, U1.12 (Q4)
/Q5: J2.6, U1.15 (Q5)
/Q6: J2.7, U1.16 (Q6)
/Q7: J2.8, U1.19 (Q7)
/Q8: J2.9, U2.2 (Q0)
/Q9: J2.10, U2.5 (Q1)
/Q10: J2.11, U2.6 (Q2)
/Q11: J2.12, U2.9 (Q3)
/Q12: J2.13, U2.12 (Q4)
/Q13: J2.14, U2.15 (Q5)
/Q14: J2.15, U2.16 (Q6)
/Q15: J2.16, U2.19 (Q7)
/~EN: U1.1 (~E), U2.1 (~E)
GND: C1.2, C2.2, U1.10 (GND), U2.10 (GND)
VCC: C1.1, C2.1, U1.20 (VCC), U2.20 (VCC)
